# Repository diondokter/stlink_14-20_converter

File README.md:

# stlink_14-20_converter
A converter pcb design to go from the 20-pin connector to the V3's 14-pin connector and vice versa

I don't really know eagle, but I think this is all you need for this to make this connector.
If you don't, just message me and I'll try to help!

You're free to use this design for whatever, just don't hold me liable for anything.
If you really want me to put up a licence, then contact me with a suggestion. All the default ones are for software...

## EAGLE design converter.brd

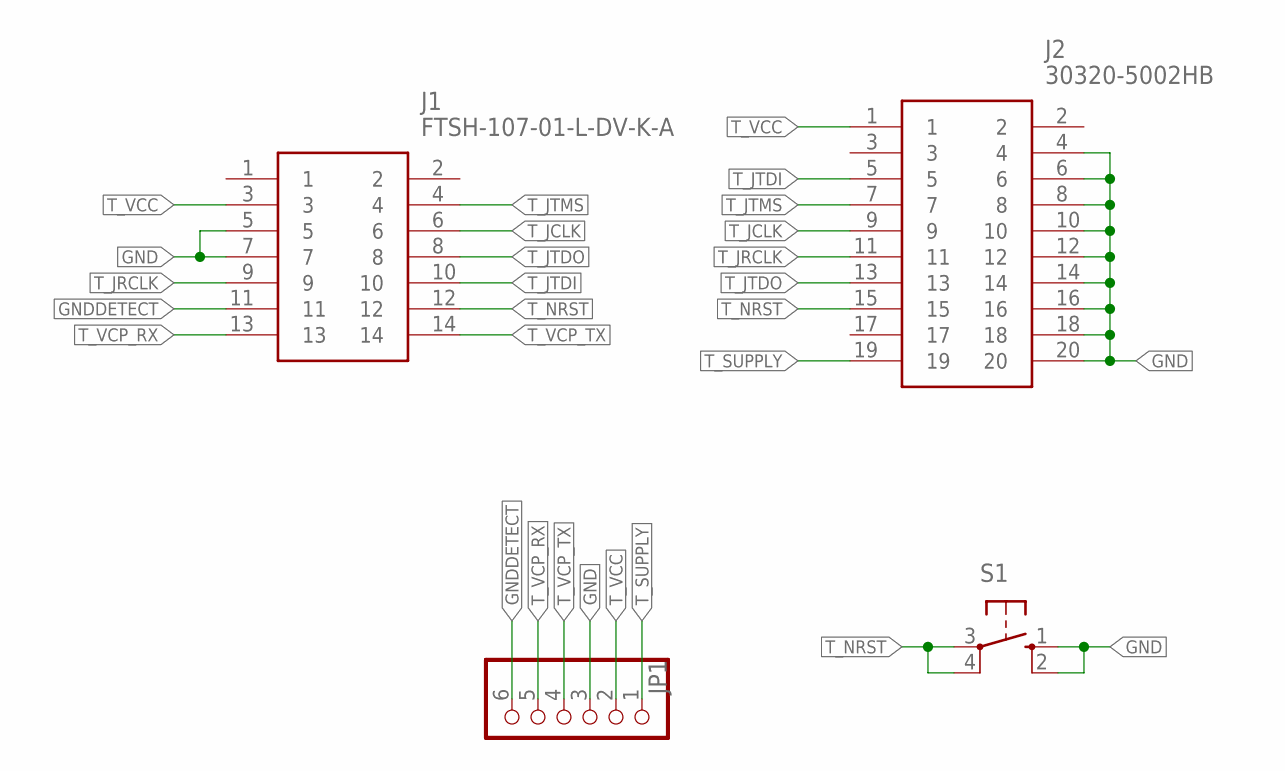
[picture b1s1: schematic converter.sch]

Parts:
J1: FTSH-107-01-L-DV-K-A; FTSH10701LDVKA
J2: 30320-5002HB; 303205002HB
JP1: PINHD-1X6; 1X06
S1: 10-XX; B3F-10XX

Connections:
GND: J1.5, J1.7, J2.4, J2.6, J2.8, J2.10, J2.12, J2.14, J2.16, J2.18, J2.20, JP1.3, S1.1 (S), S1.2 (S1)
GNDDETECT: J1.11, JP1.6
T_JCLK: J1.6, J2.9
T_JRCLK: J1.9, J2.11
T_JTDI: J1.10, J2.5
T_JTDO: J1.8, J2.13
T_JTMS: J1.4, J2.7
T_NRST: J1.12, J2.15, S1.3, S1.4 (P1)
T_SUPPLY: J2.19, JP1.1
T_VCC: J1.3, J2.1, JP1.2
T_VCP_RX: J1.13, JP1.5
T_VCP_TX: J1.14, JP1.4

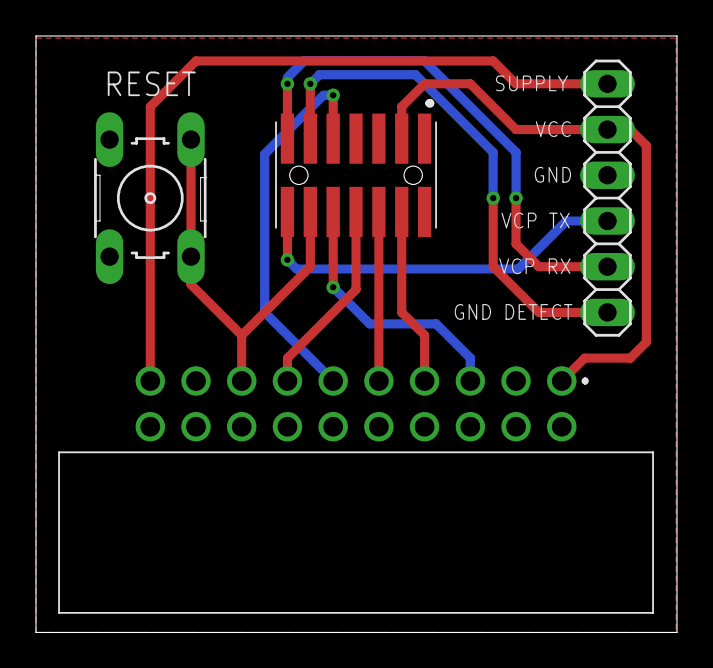
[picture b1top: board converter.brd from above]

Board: 2 copper layers, 35.6 x 33.1 mm, 4 parts (0 on the bottom side), 12 nets.

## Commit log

2020-12-18 no message
